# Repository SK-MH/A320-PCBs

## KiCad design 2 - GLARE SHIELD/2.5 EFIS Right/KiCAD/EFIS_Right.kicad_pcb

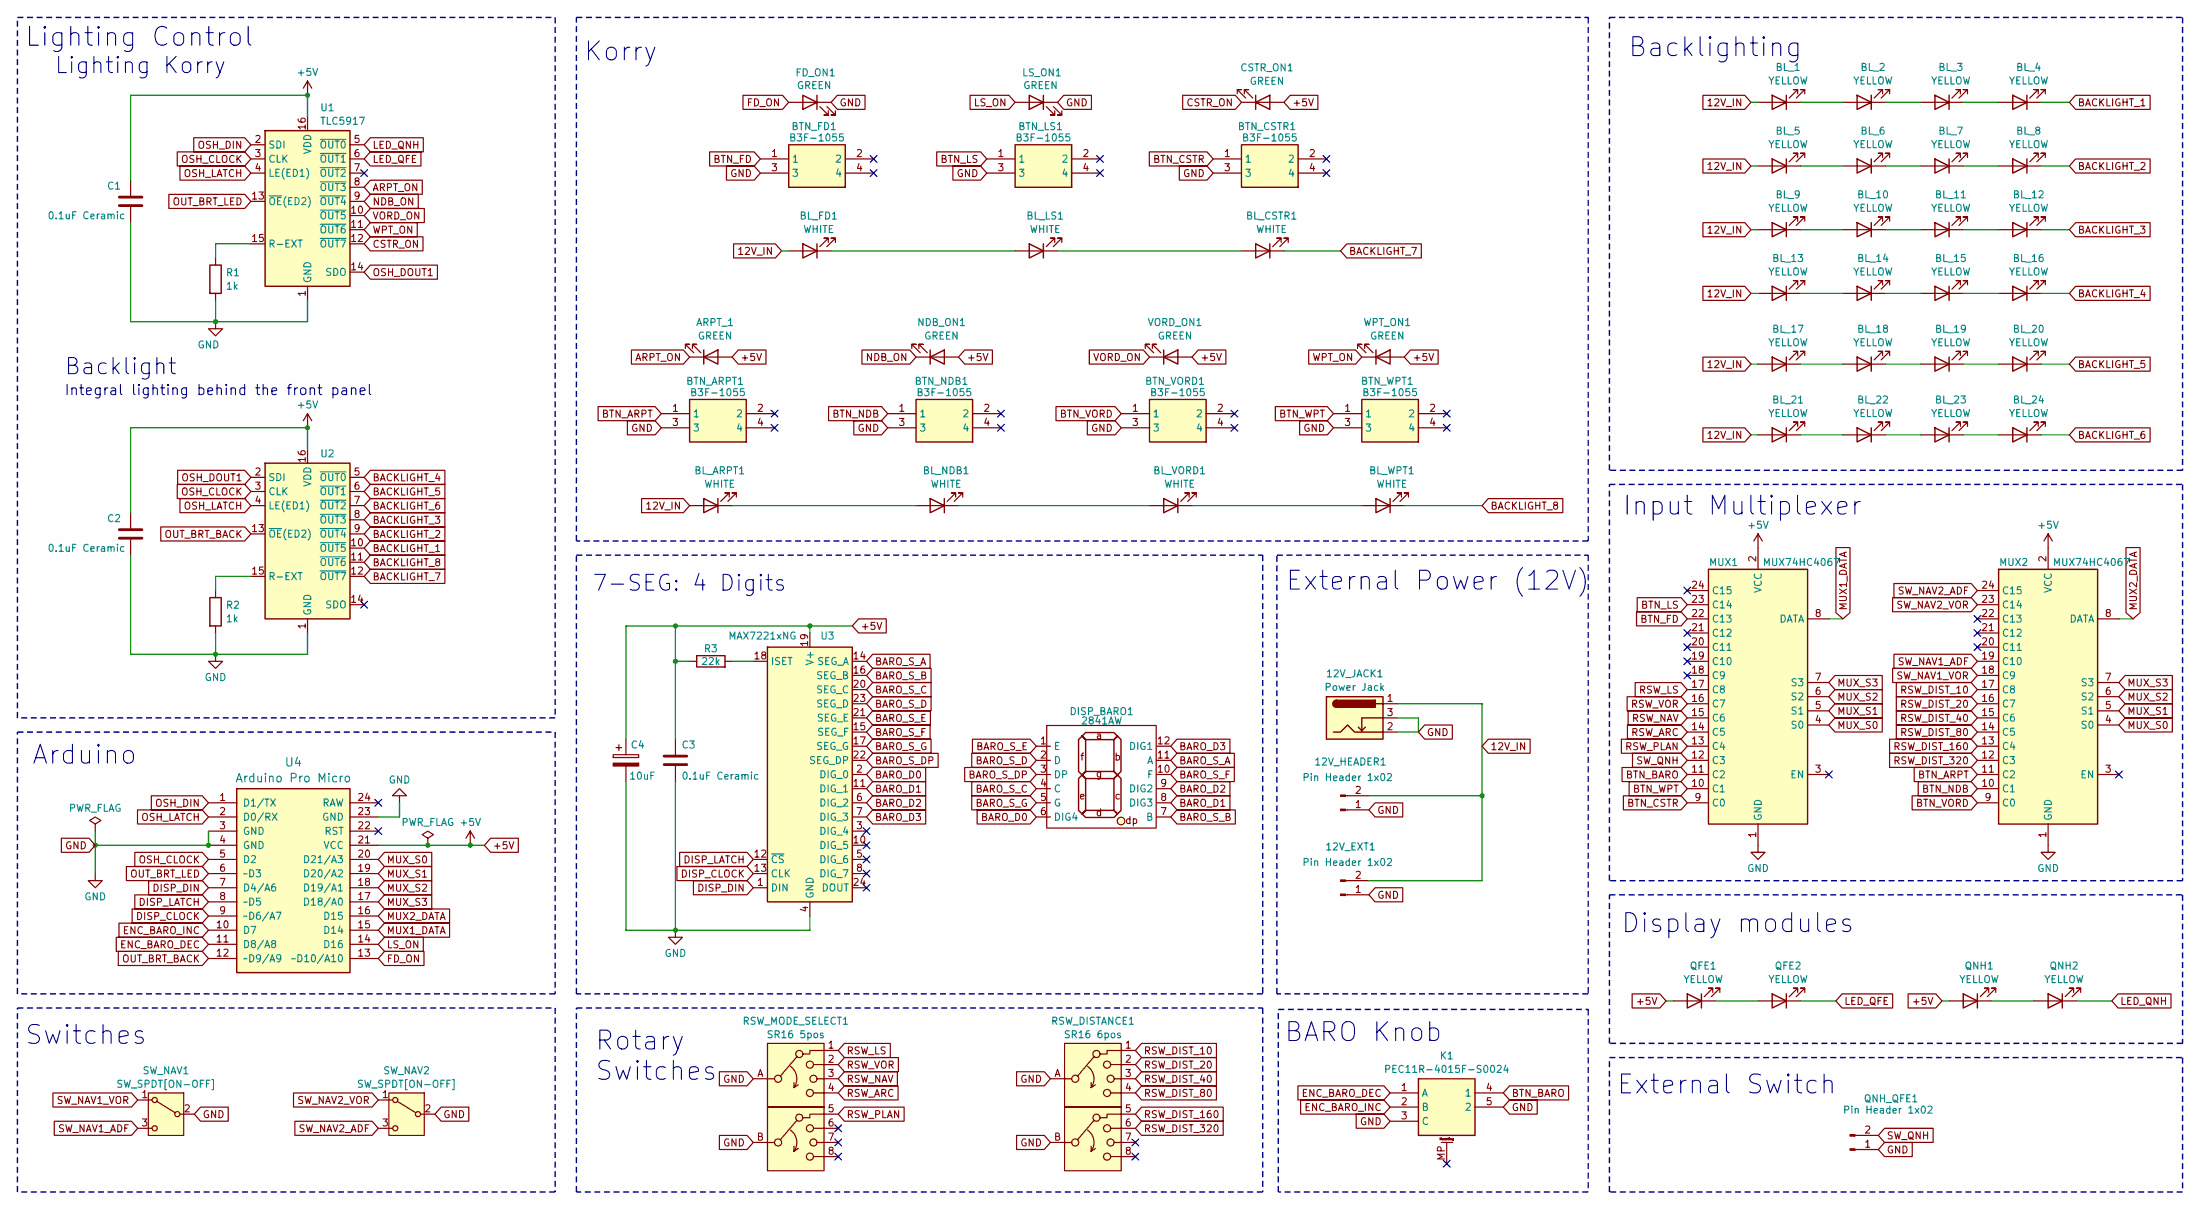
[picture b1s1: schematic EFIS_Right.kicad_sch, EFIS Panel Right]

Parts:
12V_EXT1, 12V_HEADER1: Pin Header 1x02; JST_EH_B2B-EH-A_1x02_P2.50mm_Vertical
12V_JACK1: Power Jack; BarrelJack_Horizontal
ARPT_1: GREEN; LED_D3.0mm
BL_1, BL_2, BL_3, BL_4, BL_5, BL_6, BL_7, BL_8, BL_9, BL_10, BL_11, BL_12, BL_13, BL_14, BL_15, BL_16, BL_17, BL_18, BL_19, BL_20, BL_21, BL_22, BL_23, BL_24: YELLOW; LED_D3.0mm
BL_ARPT1: WHITE; LED_D3.0mm
BL_CSTR1: WHITE; LED_D3.0mm
BL_FD1: WHITE; LED_D3.0mm
BL_LS1: WHITE; LED_D3.0mm
BL_NDB1: WHITE; LED_D3.0mm
BL_VORD1: WHITE; LED_D3.0mm
BL_WPT1: WHITE; LED_D3.0mm
BTN_ARPT1: B3F-1055; B3F1000; Mouser Part Number 653-B3F-1055
BTN_CSTR1: B3F-1055; B3F1000; Mouser Part Number 653-B3F-1055
BTN_FD1: B3F-1055; B3F1000; Mouser Part Number 653-B3F-1055
BTN_LS1: B3F-1055; B3F1000; Mouser Part Number 653-B3F-1055
BTN_NDB1: B3F-1055; B3F1000; Mouser Part Number 653-B3F-1055
BTN_VORD1: B3F-1055; B3F1000; Mouser Part Number 653-B3F-1055
BTN_WPT1: B3F-1055; B3F1000; Mouser Part Number 653-B3F-1055
C1, C2, C3: 0.1uF Ceramic; C_Disc_D3.0mm_W1.6mm_P2.50mm
C4: 10uF; CP_Radial_D4.0mm_P1.50mm
CSTR_ON1: GREEN; LED_D3.0mm
DISP_BARO1: 2841AW
FD_ON1: GREEN; LED_D3.0mm
K1: PEC11R-4015F-S0024; PEC12R-4XXXF-SXXXX_1; Mouser Part Number 652-PEC11R-4015F-S24
LS_ON1: GREEN; LED_D3.0mm
MUX1, MUX2: MUX74HC4067
NDB_ON1: GREEN; LED_D3.0mm
QFE1, QFE2: YELLOW; LED_D3.0mm
QNH1, QNH2: YELLOW; LED_D3.0mm
QNH_QFE1: Pin Header 1x02; JST_EH_B2B-EH-A_1x02_P2.50mm_Vertical
R1, R2: 1k; R_Axial_DIN0204_L3.6mm_D1.6mm_P7.62mm_Horizontal
R3: 22k; R_Axial_DIN0204_L3.6mm_D1.6mm_P7.62mm_Horizontal
RSW_DISTANCE1: SR16 6pos; SR16-AB
RSW_MODE_SELECT1: SR16 5pos; SR16-AB
SW_NAV1, SW_NAV2: SW_SPDT[ON-OFF]; T80-Z1
U1, U2: TLC5917; DIP-16_W7.62mm
U3: MAX7221xNG; DIP-24_W7.62mm
U4: Arduino Pro Micro; Sparkfun_Pro_Micro
VORD_ON1: GREEN; LED_D3.0mm
WPT_ON1: GREEN; LED_D3.0mm

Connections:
12V_IN: 12V_EXT1.2, 12V_HEADER1.2, 12V_JACK1.1, BL_1.2 (A), BL_5.2 (A), BL_9.2 (A), BL_13.2 (A), BL_17.2 (A), BL_21.2 (A), BL_ARPT1.2 (A), BL_FD1.2 (A)
+5V: ARPT_1.2 (A), C1.1, C2.1, C3.1, C4.1, CSTR_ON1.2 (A), MUX1.2 (VCC), MUX2.2 (VCC), NDB_ON1.2 (A), QFE1.2 (A), QNH1.2 (A), R3.1, U1.16 (VDD), U2.16 (VDD), U3.19 (V+), U4.21 (VCC), VORD_ON1.2 (A), WPT_ON1.2 (A)
ARPT_ON: ARPT_1.1 (K), U1.8 (~OUT3)
BACKLIGHT_1: BL_4.1 (K), U2.10 (~OUT5)
BACKLIGHT_2: BL_8.1 (K), U2.9 (~OUT4)
BACKLIGHT_3: BL_12.1 (K), U2.8 (~OUT3)
BACKLIGHT_4: BL_16.1 (K), U2.5 (~OUT0)
BACKLIGHT_5: BL_20.1 (K), U2.6 (~OUT1)
BACKLIGHT_6: BL_24.1 (K), U2.7 (~OUT2)
BACKLIGHT_7: BL_CSTR1.1 (K), U2.12 (~OUT7)
BACKLIGHT_8: BL_WPT1.1 (K), U2.11 (~OUT6)
BARO_D0: DISP_BARO1.6 (DIG4), U3.2 (DIG_0)
BARO_D1: DISP_BARO1.8 (DIG3), U3.11 (DIG_1)
BARO_D2: DISP_BARO1.9 (DIG2), U3.6 (DIG_2)
BARO_D3: DISP_BARO1.12 (DIG1), U3.7 (DIG_3)
BARO_S_A: DISP_BARO1.11 (A), U3.14 (SEG_A)
BARO_S_B: DISP_BARO1.7 (B), U3.16 (SEG_B)
BARO_S_C: DISP_BARO1.4 (C), U3.20 (SEG_C)
BARO_S_D: DISP_BARO1.2 (D), U3.23 (SEG_D)
BARO_S_DP: DISP_BARO1.3 (DP), U3.22 (SEG_DP)
BARO_S_E: DISP_BARO1.1 (E), U3.21 (SEG_E)
BARO_S_F: DISP_BARO1.10 (F), U3.15 (SEG_F)
BARO_S_G: DISP_BARO1.5 (G), U3.17 (SEG_G)
BTN_ARPT: BTN_ARPT1.1, MUX2.11 (C2)
BTN_BARO: K1.4 (1), MUX1.11 (C2)
BTN_CSTR: BTN_CSTR1.1, MUX1.9 (C0)
BTN_FD: BTN_FD1.1, MUX1.22 (C13)
BTN_LS: BTN_LS1.1, MUX1.23 (C14)
BTN_NDB: BTN_NDB1.1, MUX2.10 (C1)
BTN_VORD: BTN_VORD1.1, MUX2.9 (C0)
BTN_WPT: BTN_WPT1.1, MUX1.10 (C1)
CSTR_ON: CSTR_ON1.1 (K), U1.12 (~OUT7)
DISP_CLOCK: U3.13 (CLK), U4.9 (~D6/A7)
DISP_DIN: U3.1 (DIN), U4.7 (D4/A6)
DISP_LATCH: U3.12 (~CS), U4.8 (~D5)
ENC_BARO_DEC: K1.1 (A), U4.11 (D8/A8)
ENC_BARO_INC: K1.2 (B), U4.10 (D7)
FD_ON: FD_ON1.2 (A), U4.13 (~D10/A10)
GND: 12V_EXT1.1, 12V_HEADER1.1, 12V_JACK1.2, 12V_JACK1.3, BTN_ARPT1.3, BTN_CSTR1.3, BTN_FD1.3, BTN_LS1.3, BTN_NDB1.3, BTN_VORD1.3, BTN_WPT1.3, C1.2, C2.2, C3.2, C4.2, FD_ON1.1 (K), K1.3 (C), K1.5 (2), LS_ON1.1 (K), MUX1.1 (GND), MUX2.1 (GND), QNH_QFE1.1, R1.2, R2.2, RSW_DISTANCE1.A, RSW_DISTANCE1.B, RSW_MODE_SELECT1.A, RSW_MODE_SELECT1.B, SW_NAV1.2 (B), SW_NAV2.2 (B), U1.1 (GND), U2.1 (GND), U3.4 (GND), U3.9 (GND), U4.3 (GND), U4.4 (GND), U4.23 (GND)
LED_QFE: QFE2.1 (K), U1.6 (~OUT1)
LED_QNH: QNH2.1 (K), U1.5 (~OUT0)
LS_ON: LS_ON1.2 (A), U4.14 (D16)
MUX1_DATA: MUX1.8 (DATA), U4.15 (D14)
MUX2_DATA: MUX2.8 (DATA), U4.16 (D15)
MUX_S0: MUX1.4 (S0), MUX2.4 (S0), U4.20 (D21/A3)
MUX_S1: MUX1.5 (S1), MUX2.5 (S1), U4.19 (D20/A2)
MUX_S2: MUX1.6 (S2), MUX2.6 (S2), U4.18 (D19/A1)
MUX_S3: MUX1.7 (S3), MUX2.7 (S3), U4.17 (D18/A0)
NDB_ON: NDB_ON1.1 (K), U1.9 (~OUT4)
unnamed: BL_1.1 (K), BL_2.2 (A)
unnamed: BL_2.1 (K), BL_3.2 (A)
unnamed: BL_3.1 (K), BL_4.2 (A)
unnamed: BL_5.1 (K), BL_6.2 (A)
unnamed: BL_6.1 (K), BL_7.2 (A)
unnamed: BL_7.1 (K), BL_8.2 (A)
unnamed: BL_9.1 (K), BL_10.2 (A)
unnamed: BL_10.1 (K), BL_11.2 (A)
unnamed: BL_11.1 (K), BL_12.2 (A)
unnamed: BL_13.1 (K), BL_14.2 (A)
unnamed: BL_14.1 (K), BL_15.2 (A)
unnamed: BL_15.1 (K), BL_16.2 (A)
unnamed: BL_17.1 (K), BL_18.2 (A)
unnamed: BL_18.1 (K), BL_19.2 (A)
unnamed: BL_19.1 (K), BL_20.2 (A)
unnamed: BL_21.1 (K), BL_22.2 (A)
unnamed: BL_22.1 (K), BL_23.2 (A)
unnamed: BL_23.1 (K), BL_24.2 (A)
unnamed: BL_ARPT1.1 (K), BL_NDB1.2 (A)
unnamed: BL_CSTR1.2 (A), BL_LS1.1 (K)
unnamed: BL_FD1.1 (K), BL_LS1.2 (A)
unnamed: BL_NDB1.1 (K), BL_VORD1.2 (A)
unnamed: BL_VORD1.1 (K), BL_WPT1.2 (A)
unnamed: QFE1.1 (K), QFE2.2 (A)
unnamed: QNH1.1 (K), QNH2.2 (A)
unnamed: R1.1, U1.15 (R-EXT)
unnamed: R2.1, U2.15 (R-EXT)
unnamed: R3.2, U3.18 (ISET)
OSH_CLOCK: U1.3 (CLK), U2.3 (CLK), U4.5 (D2)
OSH_DIN: U1.2 (SDI), U4.1 (D1/TX)
OSH_DOUT1: U1.14 (SDO), U2.2 (SDI)
OSH_LATCH: U1.4 (LE(ED1)), U2.4 (LE(ED1)), U4.2 (D0/RX)
OUT_BRT_BACK: U2.13 (~OE(ED2)), U4.12 (~D9/A9)
OUT_BRT_LED: U1.13 (~OE(ED2)), U4.6 (~D3)
RSW_ARC: MUX1.14 (C5), RSW_MODE_SELECT1.4
RSW_DIST_10: MUX2.17 (C8), RSW_DISTANCE1.1
RSW_DIST_20: MUX2.16 (C7), RSW_DISTANCE1.2
RSW_DIST_40: MUX2.15 (C6), RSW_DISTANCE1.3
RSW_DIST_80: MUX2.14 (C5), RSW_DISTANCE1.4
RSW_DIST_160: MUX2.13 (C4), RSW_DISTANCE1.5
RSW_DIST_320: MUX2.12 (C3), RSW_DISTANCE1.6
RSW_LS: MUX1.17 (C8), RSW_MODE_SELECT1.1
RSW_NAV: MUX1.15 (C6), RSW_MODE_SELECT1.3
RSW_PLAN: MUX1.13 (C4), RSW_MODE_SELECT1.5
RSW_VOR: MUX1.16 (C7), RSW_MODE_SELECT1.2
SW_NAV1_ADF: MUX2.19 (C10), SW_NAV1.3 (C)
SW_NAV1_VOR: MUX2.18 (C9), SW_NAV1.1 (A)
SW_NAV2_ADF: MUX2.24 (C15), SW_NAV2.3 (C)
SW_NAV2_VOR: MUX2.23 (C14), SW_NAV2.1 (A)
SW_QNH: MUX1.12 (C3), QNH_QFE1.2
VORD_ON: U1.10 (~OUT5), VORD_ON1.1 (K)
WPT_ON: U1.11 (~OUT6), WPT_ON1.1 (K)

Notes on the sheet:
Switches
Backlighting
7-SEG: 4 Digits
Arduino
BARO Knob
Display modules
Rotary Switches
Korry
External Switch
Input Multiplexer
External Power (12V)
Lighting Korry
Lighting Control
Integral lighting behind the front panel
Backlight

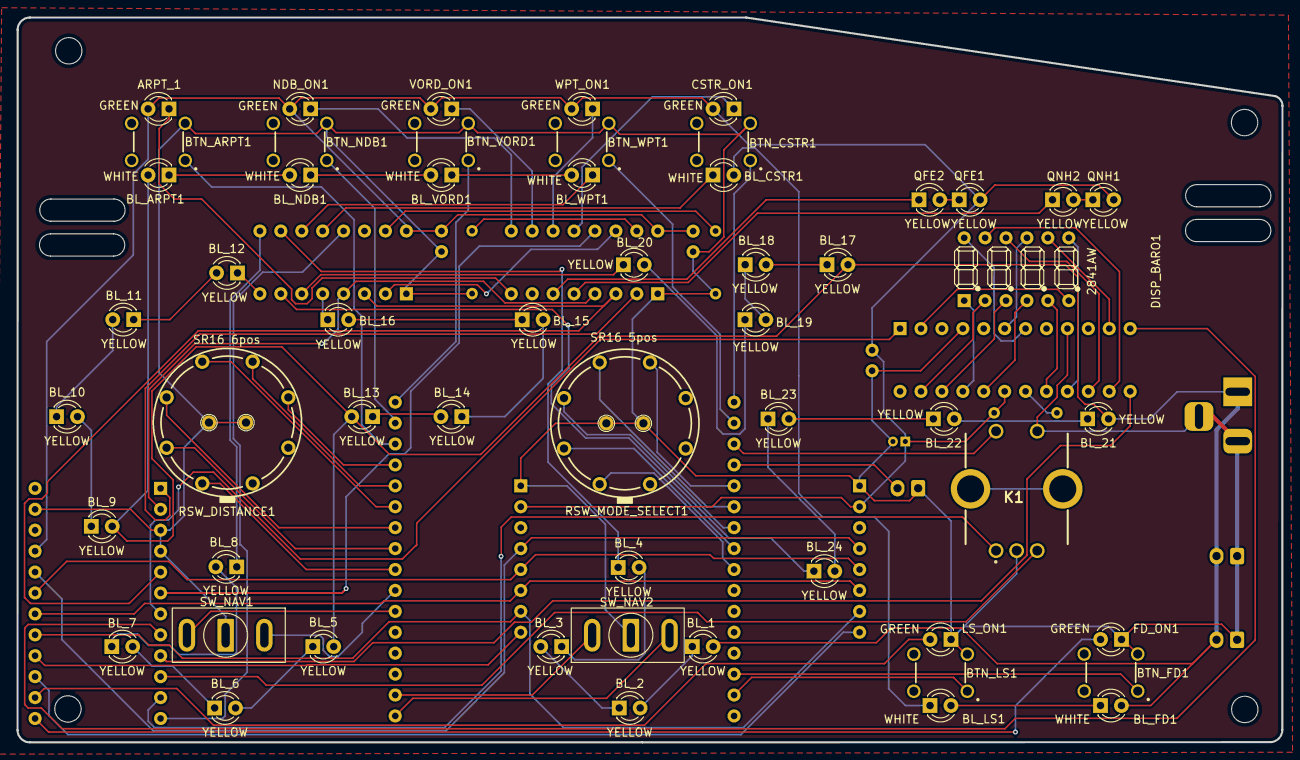
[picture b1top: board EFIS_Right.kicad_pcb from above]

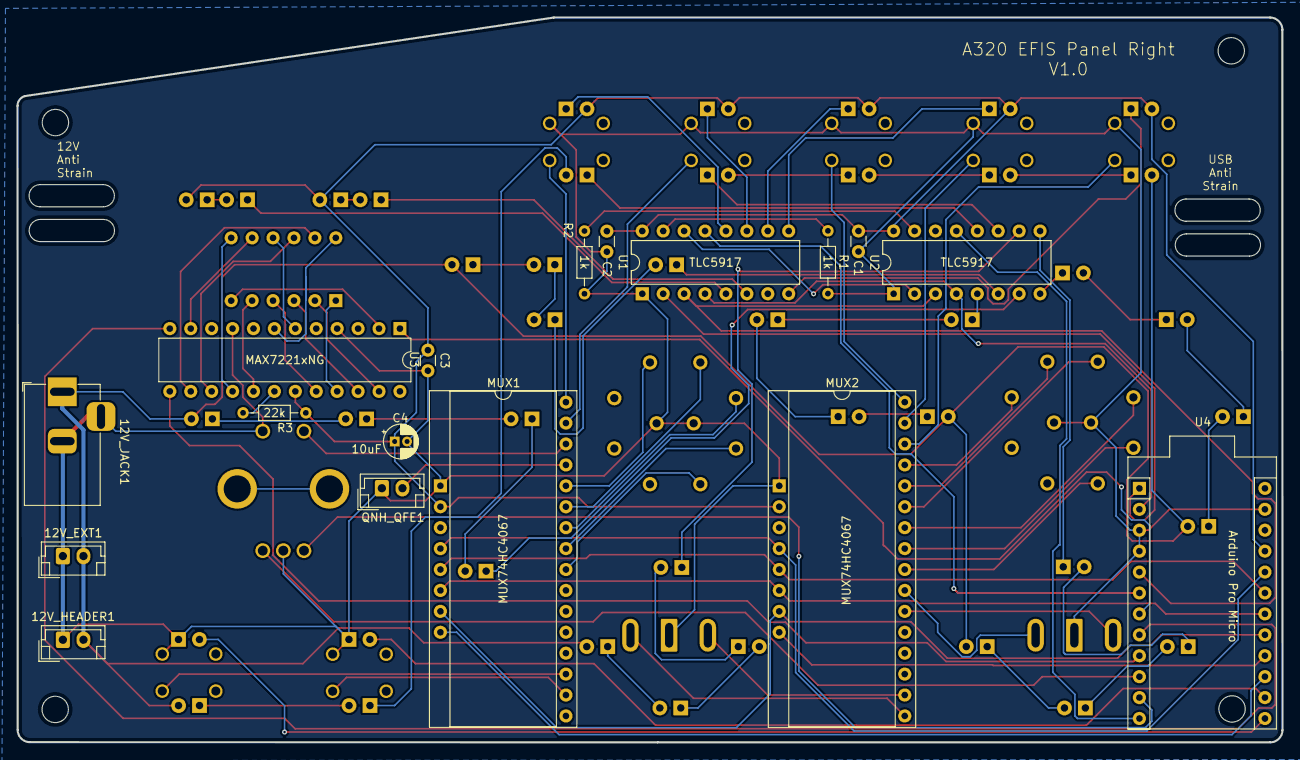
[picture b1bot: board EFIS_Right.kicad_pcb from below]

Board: 2 copper layers, 153.6 x 88.0 mm, 72 parts (17 on the bottom side), 101 nets.

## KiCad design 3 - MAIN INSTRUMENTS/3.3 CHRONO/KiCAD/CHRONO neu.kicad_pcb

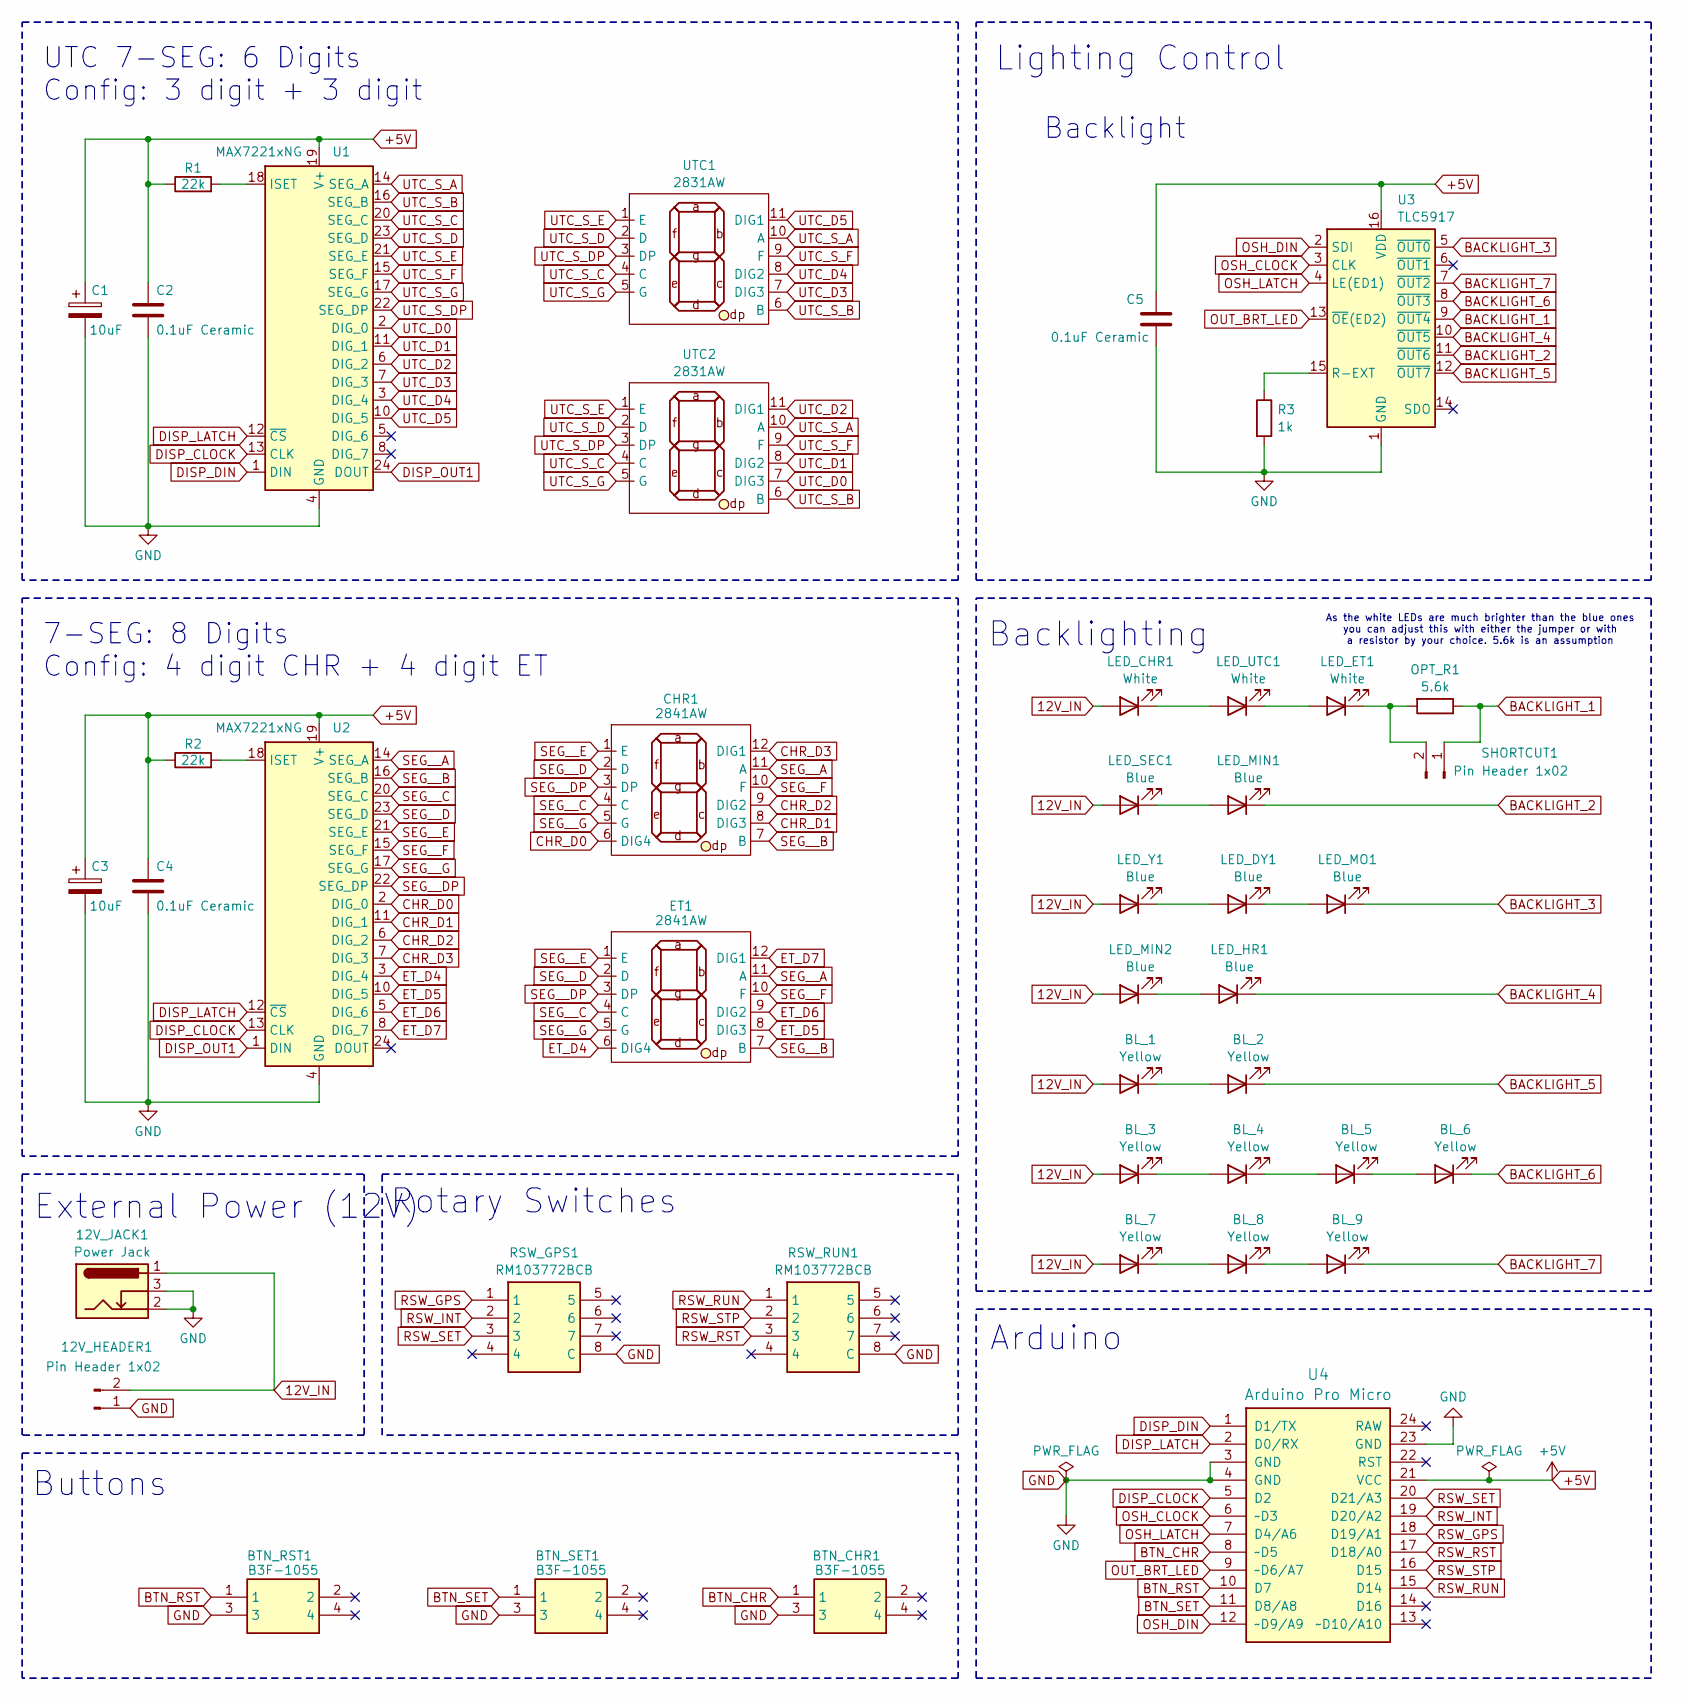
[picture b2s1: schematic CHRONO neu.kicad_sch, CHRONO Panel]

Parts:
12V_HEADER1: Pin Header 1x02; JST_EH_B2B-EH-A_1x02_P2.50mm_Vertical
12V_JACK1: Power Jack; BarrelJack_Horizontal
BL_1, BL_2, BL_3, BL_4, BL_5, BL_6, BL_7, BL_8, BL_9: Yellow; LED_D3.0mm
BTN_CHR1: B3F-1055; B3F1000; Mouser Part Number 653-B3F-1055
BTN_RST1: B3F-1055; B3F1000; Mouser Part Number 653-B3F-1055
BTN_SET1: B3F-1055; B3F1000; Mouser Part Number 653-B3F-1055
C1, C3: 10uF; CP_Radial_D4.0mm_P1.50mm
C2, C4, C5: 0.1uF Ceramic; C_Disc_D3.0mm_W1.6mm_P2.50mm
CHR1: 2841AW
ET1: 2841AW
LED_CHR1: White; LED_D3.0mm
LED_DY1: Blue; LED_D3.0mm
LED_ET1: White; LED_D3.0mm
LED_HR1: Blue; LED_D3.0mm
LED_MIN1, LED_MIN2: Blue; LED_D3.0mm
LED_MO1: Blue; LED_D3.0mm
LED_SEC1: Blue; LED_D3.0mm
LED_UTC1: White; LED_D3.0mm
LED_Y1: Blue; LED_D3.0mm
OPT_R1: 5.6k; R_Axial_DIN0204_L3.6mm_D1.6mm_P7.62mm_Horizontal
R1, R2: 22k; R_Axial_DIN0204_L3.6mm_D1.6mm_P7.62mm_Horizontal
R3: 1k; R_Axial_DIN0204_L3.6mm_D1.6mm_P7.62mm_Horizontal
RSW_GPS1: RM103772BCB; myRM103772BCB; Mouser Part Number 611-RM103772BCB
RSW_RUN1: RM103772BCB; myRM103772BCB; Mouser Part Number 611-RM103772BCB
SHORTCUT1: Pin Header 1x02; PinHeader_1x02_P2.54mm_Vertical
U1, U2: MAX7221xNG; DIP-24_W7.62mm
U3: TLC5917; DIP-16_W7.62mm
U4: Arduino Pro Micro; Sparkfun_Pro_Micro
UTC1, UTC2: 2831AW

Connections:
12V_IN: 12V_HEADER1.2, 12V_JACK1.1, BL_1.2 (A), BL_3.2 (A), BL_7.2 (A), LED_CHR1.2 (A), LED_MIN2.2 (A), LED_SEC1.2 (A), LED_Y1.2 (A)
+5V: C1.1, C2.1, C3.1, C4.1, C5.1, R1.1, R2.1, U1.19 (V+), U2.19 (V+), U3.16 (VDD), U4.21 (VCC)
BACKLIGHT_1: OPT_R1.1, SHORTCUT1.1, U3.9 (~OUT4)
BACKLIGHT_2: LED_MIN1.1 (K), U3.11 (~OUT6)
BACKLIGHT_3: LED_MO1.1 (K), U3.5 (~OUT0)
BACKLIGHT_4: LED_HR1.1 (K), U3.10 (~OUT5)
BACKLIGHT_5: BL_2.1 (K), U3.12 (~OUT7)
BACKLIGHT_6: BL_6.1 (K), U3.8 (~OUT3)
BACKLIGHT_7: BL_9.1 (K), U3.7 (~OUT2)
BTN_CHR: BTN_CHR1.1, U4.8 (~D5)
BTN_RST: BTN_RST1.1, U4.10 (D7)
BTN_SET: BTN_SET1.1, U4.11 (D8/A8)
CHR_D0: CHR1.6 (DIG4), U2.2 (DIG_0)
CHR_D1: CHR1.8 (DIG3), U2.11 (DIG_1)
CHR_D2: CHR1.9 (DIG2), U2.6 (DIG_2)
CHR_D3: CHR1.12 (DIG1), U2.7 (DIG_3)
DISP_CLOCK: U1.13 (CLK), U2.13 (CLK), U4.5 (D2)
DISP_DIN: U1.1 (DIN), U4.1 (D1/TX)
DISP_LATCH: U1.12 (~CS), U2.12 (~CS), U4.2 (D0/RX)
DISP_OUT1: U1.24 (DOUT), U2.1 (DIN)
ET_D4: ET1.6 (DIG4), U2.3 (DIG_4)
ET_D5: ET1.8 (DIG3), U2.10 (DIG_5)
ET_D6: ET1.9 (DIG2), U2.5 (DIG_6)
ET_D7: ET1.12 (DIG1), U2.8 (DIG_7)
GND: 12V_HEADER1.1, 12V_JACK1.2, 12V_JACK1.3, BTN_CHR1.3, BTN_RST1.3, BTN_SET1.3, C1.2, C2.2, C3.2, C4.2, C5.2, R3.2, RSW_GPS1.8 (C), RSW_RUN1.8 (C), U1.4 (GND), U1.9 (GND), U2.4 (GND), U2.9 (GND), U3.1 (GND), U4.3 (GND), U4.4 (GND), U4.23 (GND)
unnamed: BL_1.1 (K), BL_2.2 (A)
unnamed: BL_3.1 (K), BL_4.2 (A)
unnamed: BL_4.1 (K), BL_5.2 (A)
unnamed: BL_5.1 (K), BL_6.2 (A)
unnamed: BL_7.1 (K), BL_8.2 (A)
unnamed: BL_8.1 (K), BL_9.2 (A)
unnamed: LED_CHR1.1 (K), LED_UTC1.2 (A)
unnamed: LED_DY1.2 (A), LED_Y1.1 (K)
unnamed: LED_DY1.1 (K), LED_MO1.2 (A)
unnamed: LED_ET1.2 (A), LED_UTC1.1 (K)
unnamed: LED_ET1.1 (K), OPT_R1.2, SHORTCUT1.2
unnamed: LED_HR1.2 (A), LED_MIN2.1 (K)
unnamed: LED_MIN1.2 (A), LED_SEC1.1 (K)
unnamed: R1.2, U1.18 (ISET)
unnamed: R2.2, U2.18 (ISET)
unnamed: R3.1, U3.15 (R-EXT)
OSH_CLOCK: U3.3 (CLK), U4.6 (~D3)
OSH_DIN: U3.2 (SDI), U4.12 (~D9/A9)
OSH_LATCH: U3.4 (LE(ED1)), U4.7 (D4/A6)
OUT_BRT_LED: U3.13 (~OE(ED2)), U4.9 (~D6/A7)
RSW_GPS: RSW_GPS1.1, U4.18 (D19/A1)
RSW_INT: RSW_GPS1.2, U4.19 (D20/A2)
RSW_RST: RSW_RUN1.3, U4.17 (D18/A0)
RSW_RUN: RSW_RUN1.1, U4.15 (D14)
RSW_SET: RSW_GPS1.3, U4.20 (D21/A3)
RSW_STP: RSW_RUN1.2, U4.16 (D15)
SEG__A: CHR1.11 (A), ET1.11 (A), U2.14 (SEG_A)
SEG__B: CHR1.7 (B), ET1.7 (B), U2.16 (SEG_B)
SEG__C: CHR1.4 (C), ET1.4 (C), U2.20 (SEG_C)
SEG__D: CHR1.2 (D), ET1.2 (D), U2.23 (SEG_D)
SEG__DP: CHR1.3 (DP), ET1.3 (DP), U2.22 (SEG_DP)
SEG__E: CHR1.1 (E), ET1.1 (E), U2.21 (SEG_E)
SEG__F: CHR1.10 (F), ET1.10 (F), U2.15 (SEG_F)
SEG__G: CHR1.5 (G), ET1.5 (G), U2.17 (SEG_G)
UTC_D0: U1.2 (DIG_0), UTC2.7 (DIG3)
UTC_D1: U1.11 (DIG_1), UTC2.8 (DIG2)
UTC_D2: U1.6 (DIG_2), UTC2.11 (DIG1)
UTC_D3: U1.7 (DIG_3), UTC1.7 (DIG3)
UTC_D4: U1.3 (DIG_4), UTC1.8 (DIG2)
UTC_D5: U1.10 (DIG_5), UTC1.11 (DIG1)
UTC_S_A: U1.14 (SEG_A), UTC1.10 (A), UTC2.10 (A)
UTC_S_B: U1.16 (SEG_B), UTC1.6 (B), UTC2.6 (B)
UTC_S_C: U1.20 (SEG_C), UTC1.4 (C), UTC2.4 (C)
UTC_S_D: U1.23 (SEG_D), UTC1.2 (D), UTC2.2 (D)
UTC_S_DP: U1.22 (SEG_DP), UTC1.3 (DP), UTC2.3 (DP)
UTC_S_E: U1.21 (SEG_E), UTC1.1 (E), UTC2.1 (E)
UTC_S_F: U1.15 (SEG_F), UTC1.9 (F), UTC2.9 (F)
UTC_S_G: U1.17 (SEG_G), UTC1.5 (G), UTC2.5 (G)

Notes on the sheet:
Arduino
External Power (12V)
Backlighting
Backlight
Rotary Switches
Lighting Control
UTC 7-SEG: 6 Digits Config: 3 digit + 3 digit
As the white LEDs are much brighter than the blue ones you can adjust this with either the jumper or with a resistor by your choice. 5.6k is an assumption
Buttons
7-SEG: 8 Digits Config: 4 digit CHR + 4 digit ET

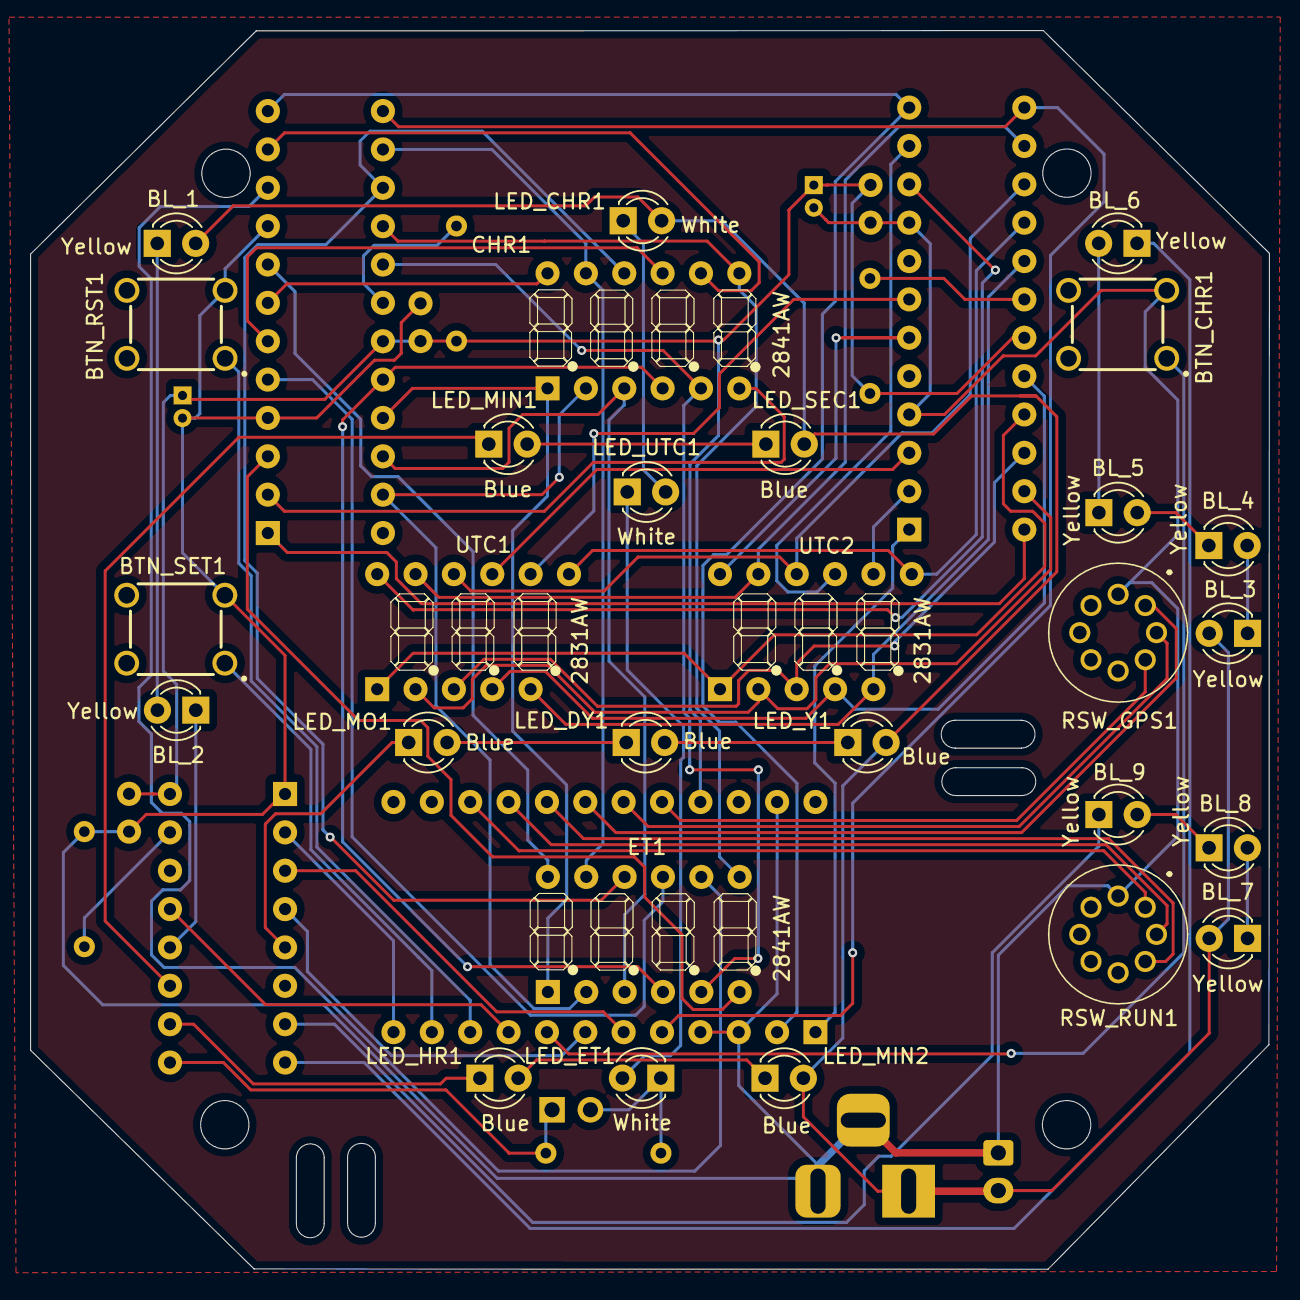
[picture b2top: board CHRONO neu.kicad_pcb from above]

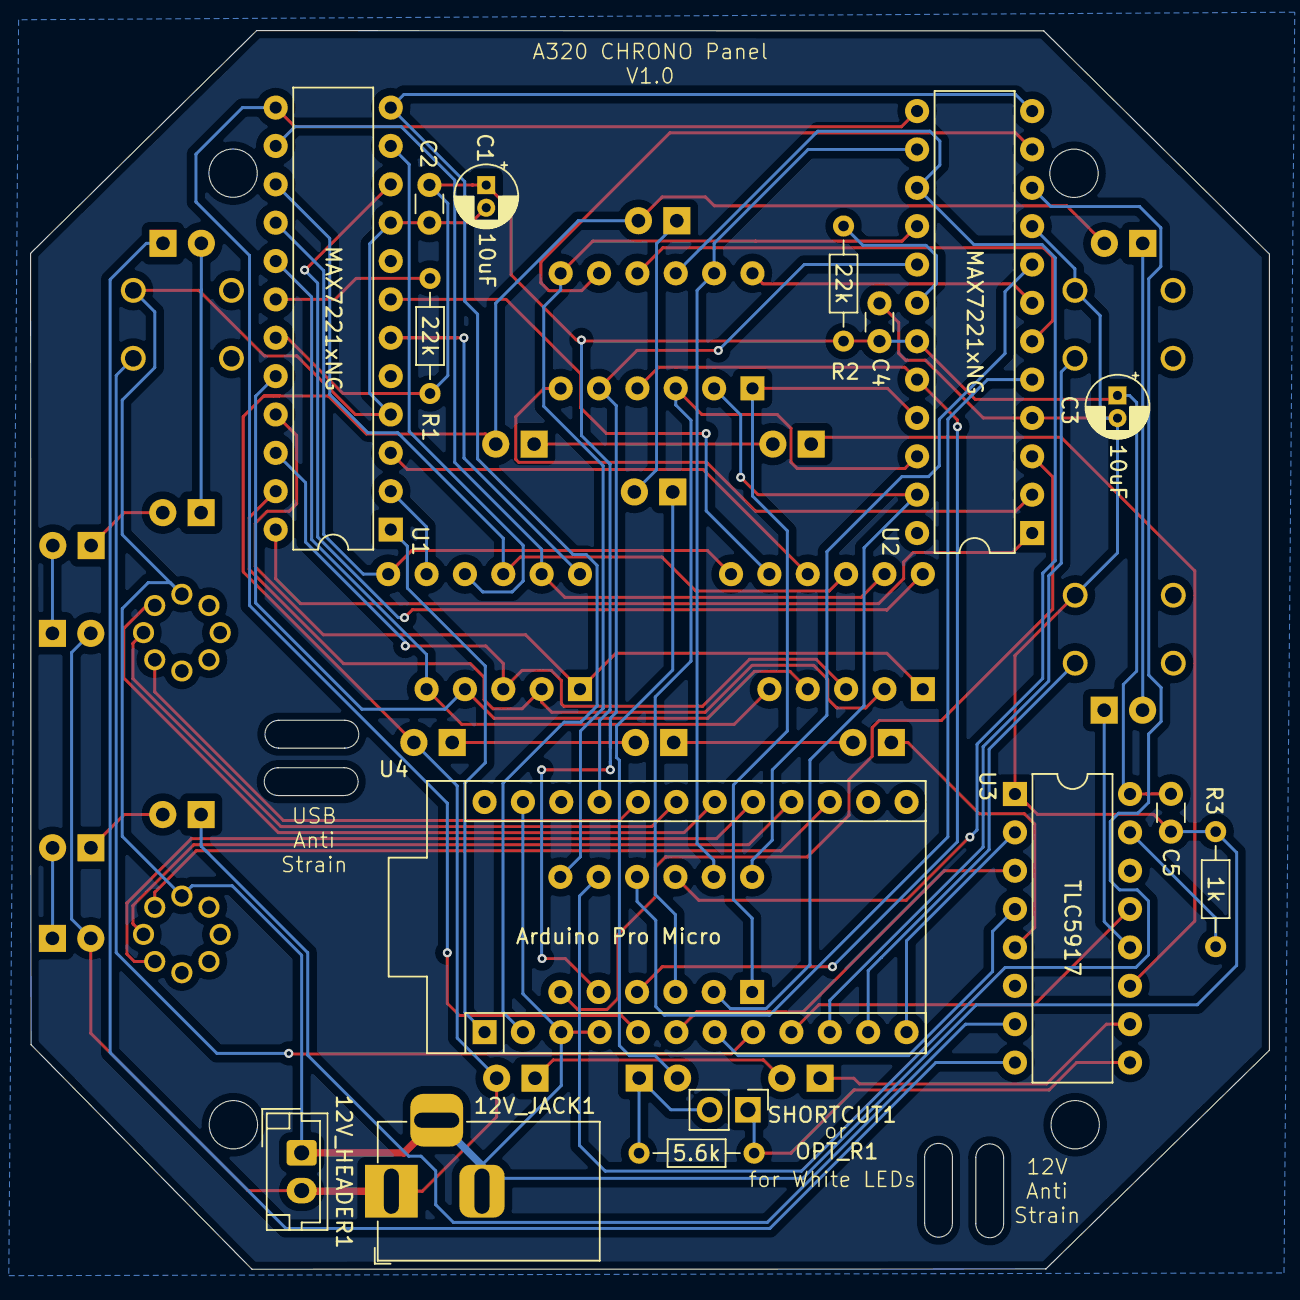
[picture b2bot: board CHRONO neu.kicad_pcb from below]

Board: 2 copper layers, 82.0 x 82.0 mm, 44 parts (16 on the bottom side), 73 nets.
